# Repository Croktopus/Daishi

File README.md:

# Daishi

http://kb.metamechs.com/daishi/

I'm redesigning the Daishi-Prime (Daishi case that uses a plate), so stay tuned for that I guess.

If you're interested in designing your own keyboard, I recommend https://github.com/ruiqimao/keyboard-pcb-guide to learn PCB design, https://beta.docs.qmk.fm/ for how to use QMK, and https://www.youtube.com/watch?v=A5bc9c3S12g&list=PL40d7srwyc_Ow4aaOGXlP2idPGwD7ruKg to get started with Fusion 360.

Other invaluable resources:
* http://www.keyboard-layout-editor.com/ to design your layout
* http://builder.swillkb.com/ to generate a plate (though I do recommend doing it manually if it's going to be more complex than a rectangle with a few holes)
* https://discordapp.com/invite/Uq7gcHh for the QMK discord (super helpful folks who are way better at this than me)
* https://www.laserboost.com/ to get a metal plate cut
* https://www.ponoko.com/ to get an acrylic plate cut
* https://jlcpcb.com/ cheapest PCB manufacturer I've found

Check the BoM to find links to places where you can buy all the components for cheaper than I was able to.

All I ask is that if you do build one of these please send me pics!

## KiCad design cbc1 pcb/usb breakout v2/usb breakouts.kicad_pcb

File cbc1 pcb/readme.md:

# Making a PCB

If you just want to have a CBC1 PCB printed, you'll want to take the gerbers.zip file to your PCB fab of choice (I recommend JLCPCB for the price), as well as the gerbers.zip in the daughterboard directory.

I've also got all the KiCad files in here if you want to play around with making your own modifications.

Once you have your PCB (unless you got it assembled for you), you get to do all the super fun SMT soldering! This is easily the worst part of the process IMO, but you can get through it in a few hours. If you haven't done this before, look up some youtube tutorials before you decide whether you want to.

Then you can tune your stabs, crimp a cable, and solder some switches (I recommend following Nathan Kim's guide for stabilizers, just without the band-aid mod).

Obviously this is super light on details, but...anything in here that you don't know how to do, just look it up. If you're still having trouble understanding something, I can answer some questions, but there are some fairly deep topics in here that already have great educational resources (EEVBlog for soldering, https://github.com/ruiqimao/keyboard-pcb-guide for KiCad, Nathan Kim's vids and streams for keeb building).

But that's pretty much the gist of it for getting a functional PCB for your Daishi build.

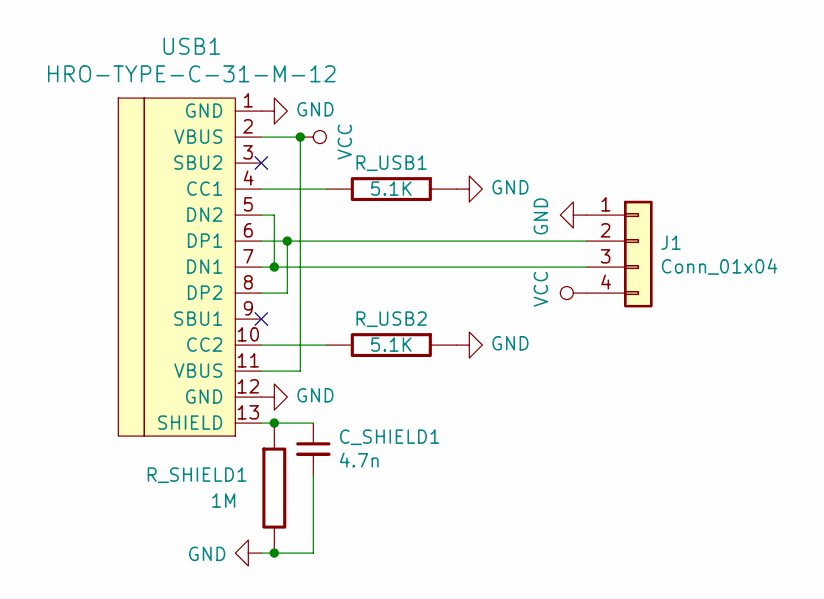
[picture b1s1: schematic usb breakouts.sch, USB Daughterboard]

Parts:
C_SHIELD1: 4.7n; C_0805_HandSoldering
J1: Conn_01x04; Pin_Header_Angled_1x04_Pitch2.54mm_centered
R_SHIELD1: 1M; R_0805_HandSoldering
R_USB1, R_USB2: 5.1K; R_0805_HandSoldering
USB1: HRO-TYPE-C-31-M-12; HRO-TYPE-C-31-M-12-HandSoldering

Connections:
GND: C_SHIELD1.2, J1.1, R_SHIELD1.2, R_USB1.1, R_USB2.1, USB1.1 (GND), USB1.12 (GND)
unnamed: C_SHIELD1.1, R_SHIELD1.1, USB1.13 (SHIELD)
unnamed: J1.2, USB1.6 (DP1), USB1.8 (DP2)
unnamed: J1.3, USB1.5 (DN2), USB1.7 (DN1)
unnamed: R_USB1.2, USB1.4 (CC1)
unnamed: R_USB2.2, USB1.10 (CC2)
VCC: J1.4, USB1.2 (VBUS), USB1.11 (VBUS)

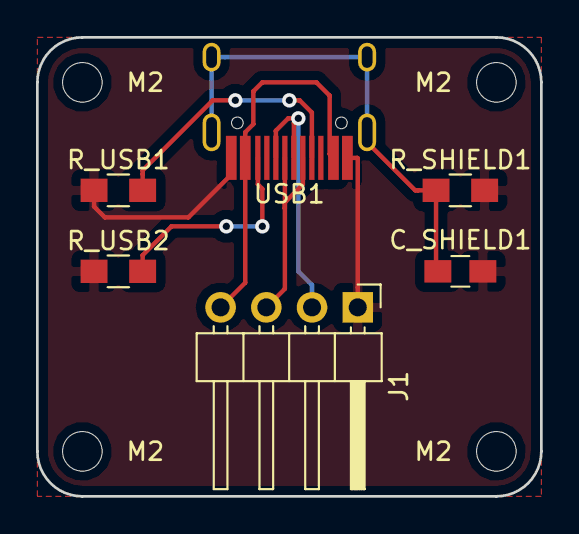
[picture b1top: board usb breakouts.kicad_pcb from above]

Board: 2 copper layers, 28.0 x 25.5 mm, 10 parts (0 on the bottom side), 7 nets.

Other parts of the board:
M2, M2#2, M2#3, M2#4: MountingHole_2.2mm_M2

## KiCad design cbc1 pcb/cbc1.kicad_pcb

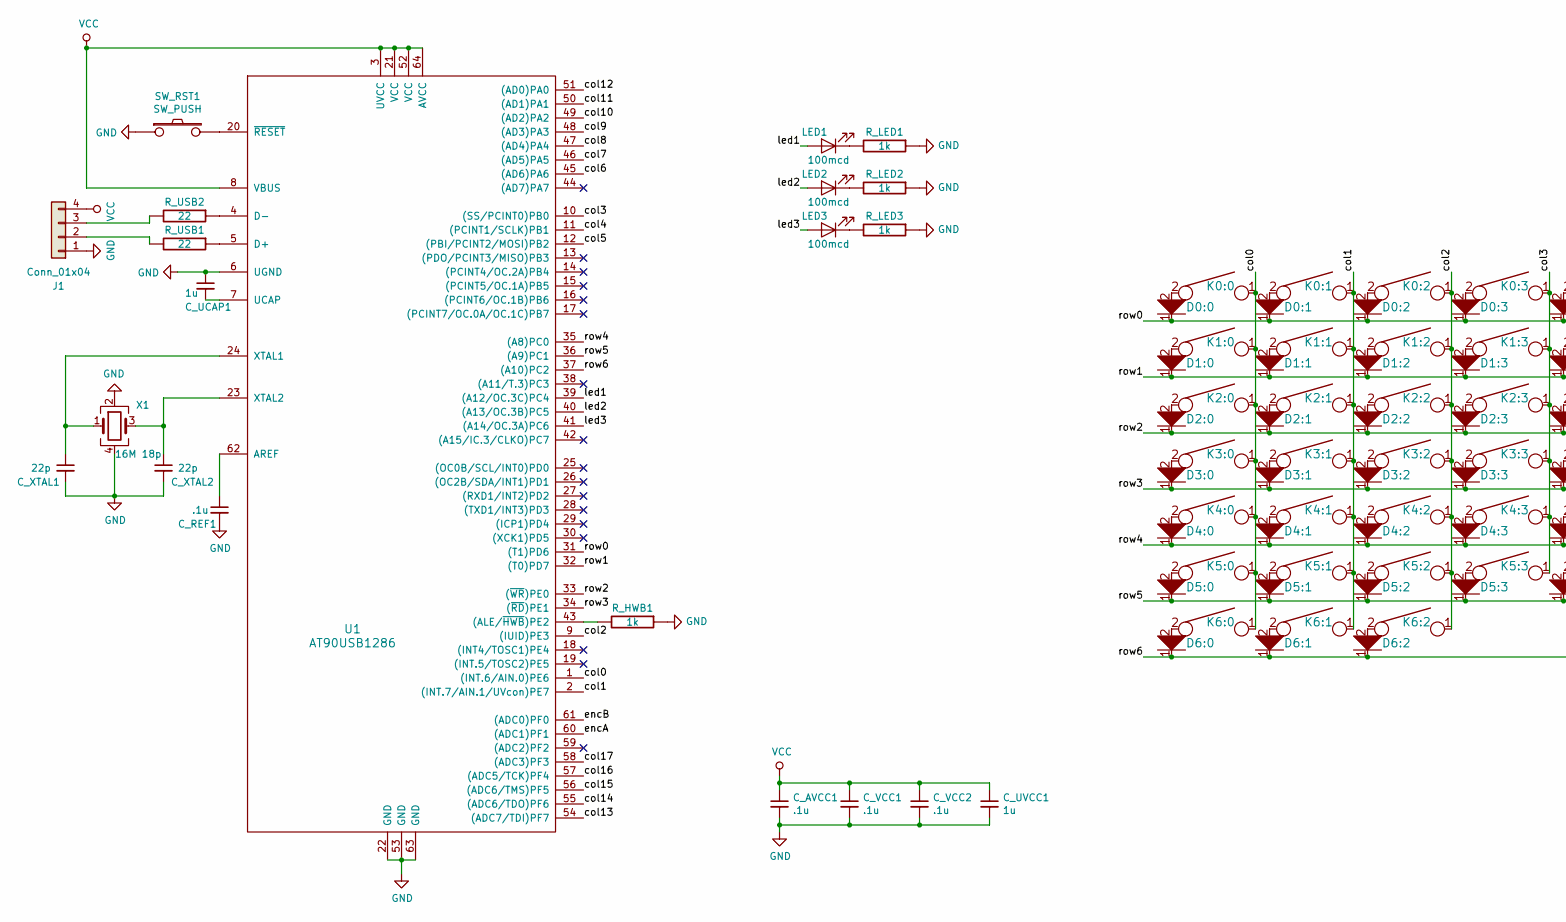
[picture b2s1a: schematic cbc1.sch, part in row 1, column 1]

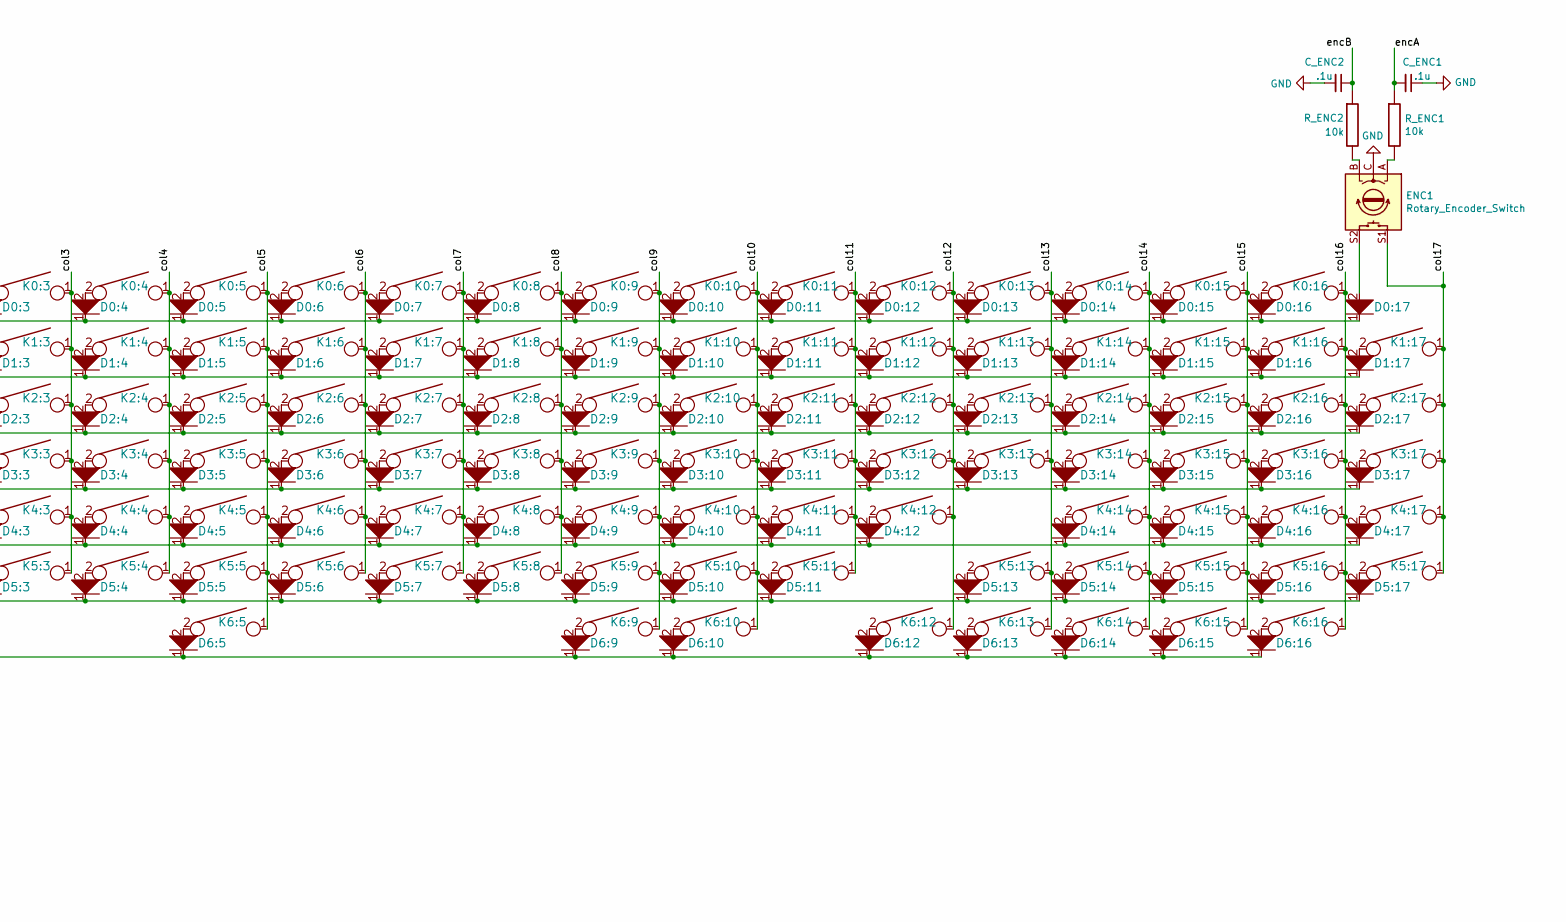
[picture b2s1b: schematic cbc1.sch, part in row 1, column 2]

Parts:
C_AVCC1: .1u; C_0805_HandSoldering
C_ENC1, C_ENC2: .1u; C_0805_HandSoldering
C_REF1: .1u; C_0805_HandSoldering
C_UCAP1: 1u; C_0805_HandSoldering
C_UVCC1: 1u; C_0805_HandSoldering
C_VCC1, C_VCC2: .1u; C_0805_HandSoldering
C_XTAL1, C_XTAL2: 22p; C_0805_HandSoldering
D0:0, D0:1, D0:2, D0:3, D0:4, D0:5, D0:6, D0:7, D0:8, D0:9, D0:10, D0:11, D0:12, D0:13, D0:14, D0:15, D0:16, D0:17, D1:0, D1:1, D1:2, D1:3, D1:4, D1:5, D1:6, D1:7, D1:8, D1:9, D1:10, D1:11, D1:12, D1:13, D1:14, D1:15, D1:16, D1:17, D2:0, D2:1, D2:2, D2:3, D2:4, D2:5, D2:6, D2:7, D2:8, D2:9, D2:10, D2:11, D2:12, D2:13, D2:14, D2:15, D2:16, D2:17, D3:0, D3:1, D3:2, D3:3, D3:4, D3:5, D3:6, D3:7, D3:8, D3:9, D3:10, D3:11, D3:12, D3:13, D3:14, D3:15, D3:16, D3:17, D4:0, D4:1, D4:2, D4:3, D4:4, D4:5, D4:6, D4:7, D4:8, D4:9, D4:10, D4:11, D4:12, D4:14, D4:15, D4:16, D4:17, D5:0, D5:1, D5:2, D5:3, D5:4, D5:5, D5:6, D5:7, D5:8, D5:9, D5:10, D5:11, D5:13, D5:14, D5:15, D5:16, D5:17, D6:0, D6:1, D6:2, D6:5, D6:9, D6:10, D6:12, D6:13, D6:14, D6:15, D6:16: D; D_SOD123_hand
ENC1: Rotary_Encoder_Switch; RotaryEncoder_Alps_EC11E-Switch_Vertical_H20mm
J1: Conn_01x04; Pin_Header_Angled_1x04_Pitch2.54mm
K0:0, K0:1, K0:2, K0:3, K0:4, K0:5, K0:6, K0:7, K0:8, K0:9, K0:10, K0:11, K0:12, K0:13, K0:14, K0:15, K0:16, K1:0, K1:1, K1:2, K1:3, K1:4, K1:5, K1:6, K1:7, K1:8, K1:9, K1:10, K1:11, K1:12, K1:13, K1:14, K1:15, K1:16, K1:17, K2:0, K2:1, K2:2, K2:3, K2:4, K2:5, K2:6, K2:7, K2:8, K2:9, K2:10, K2:11, K2:12, K2:14, K2:15, K2:16, K2:17, K3:1, K3:2, K3:3, K3:4, K3:5, K3:6, K3:7, K3:8, K3:9, K3:10, K3:11, K3:12, K3:14, K3:15, K3:16, K3:17, K4:1, K4:2, K4:3, K4:4, K4:5, K4:6, K4:7, K4:8, K4:9, K4:10, K4:11, K4:14, K4:15, K4:16, K4:17, K5:1, K5:2, K5:3, K5:4, K5:5, K5:6, K5:7, K5:8, K5:9, K5:10, K5:13, K5:14, K5:15, K5:16, K6:12, K6:13, K6:14, K6:15, K6:16: KEYSW; SMK-PCB-100-90deg
K2:13, K5:17: KEYSW; SMK-PCB-200-90deg
K3:0, K3:13, K6:9, K6:10: KEYSW; SMK-PCB-150-90deg
K4:0, K5:11: KEYSW; SMK-PCB-175-90deg
K4:12, K5:0: KEYSW; SMK-PCB-225-90deg
K6:0, K6:1, K6:2: KEYSW; SMK-PCB-125-90deg
K6:5: KEYSW; SMK-PCB-625-90deg
LED1, LED2, LED3: 100mcd; LED_0805_HandSoldering
R_ENC1, R_ENC2: 10k; R_0805_HandSoldering
R_HWB1: 1k; R_0805_HandSoldering
R_LED1, R_LED2, R_LED3: 1k; R_0805_HandSoldering
R_USB1, R_USB2: 22; R_0805_HandSoldering
SW_RST1: SW_PUSH; SW_SPST_TL3342
U1: AT90USB1286; TQFP-64_14x14mm_Pitch0.8mm
X1: 16M 18p; Crystal_SMD_SeikoEpson_FA238-4pin_3.2x2.5mm_HandSoldering

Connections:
/col0: K0:0.1, K1:0.1, K2:0.1, K3:0.1, K4:0.1, K5:0.1, K6:0.1, U1.1 ((INT.6/AIN.0)PE6)
/col1: K0:1.1, K1:1.1, K2:1.1, K3:1.1, K4:1.1, K5:1.1, K6:1.1, U1.2 ((INT.7/AIN.1/UVcon)PE7)
/col2: K0:2.1, K1:2.1, K2:2.1, K3:2.1, K4:2.1, K5:2.1, K6:2.1, U1.9 ((IUID)PE3)
/col3: K0:3.1, K1:3.1, K2:3.1, K3:3.1, K4:3.1, K5:3.1, U1.10 ((SS/PCINT0)PB0)
/col4: K0:4.1, K1:4.1, K2:4.1, K3:4.1, K4:4.1, K5:4.1, U1.11 ((PCINT1/SCLK)PB1)
/col5: K0:5.1, K1:5.1, K2:5.1, K3:5.1, K4:5.1, K5:5.1, K6:5.1, U1.12 ((PBI/PCINT2/MOSI)PB2)
/col6: K0:6.1, K1:6.1, K2:6.1, K3:6.1, K4:6.1, K5:6.1, U1.45 ((AD6)PA6)
/col7: K0:7.1, K1:7.1, K2:7.1, K3:7.1, K4:7.1, K5:7.1, U1.46 ((AD5)PA5)
/col8: K0:8.1, K1:8.1, K2:8.1, K3:8.1, K4:8.1, K5:8.1, U1.47 ((AD4)PA4)
/col9: K0:9.1, K1:9.1, K2:9.1, K3:9.1, K4:9.1, K5:9.1, K6:9.1, U1.48 ((AD3)PA3)
/col10: K0:10.1, K1:10.1, K2:10.1, K3:10.1, K4:10.1, K5:10.1, K6:10.1, U1.49 ((AD2)PA2)
/col11: K0:11.1, K1:11.1, K2:11.1, K3:11.1, K4:11.1, K5:11.1, U1.50 ((AD1)PA1)
/col12: K0:12.1, K1:12.1, K2:12.1, K3:12.1, K4:12.1, K6:12.1, U1.51 ((AD0)PA0)
/col13: K0:13.1, K1:13.1, K2:13.1, K3:13.1, K5:13.1, K6:13.1, U1.54 ((ADC7/TDI)PF7)
/col14: K0:14.1, K1:14.1, K2:14.1, K3:14.1, K4:14.1, K5:14.1, K6:14.1, U1.55 ((ADC6/TDO)PF6)
/col15: K0:15.1, K1:15.1, K2:15.1, K3:15.1, K4:15.1, K5:15.1, K6:15.1, U1.56 ((ADC6/TMS)PF5)
/col16: K0:16.1, K1:16.1, K2:16.1, K3:16.1, K4:16.1, K5:16.1, K6:16.1, U1.57 ((ADC5/TCK)PF4)
/col17: ENC1.S1, K1:17.1, K2:17.1, K3:17.1, K4:17.1, K5:17.1, U1.58 ((ADC3)PF3)
/encA: C_ENC1.2, R_ENC1.1, U1.60 ((ADC1)PF1)
/encB: C_ENC2.1, R_ENC2.1, U1.61 ((ADC0)PF0)
/led1: LED1.2 (A), U1.39 ((A12/OC.3C)PC4)
/led2: LED2.2 (A), U1.40 ((A13/OC.3B)PC5)
/led3: LED3.2 (A), U1.41 ((A14/OC.3A)PC6)
/row0: D0:0.1, D0:1.1, D0:2.1, D0:3.1, D0:4.1, D0:5.1, D0:6.1, D0:7.1, D0:8.1, D0:9.1, D0:10.1, D0:11.1, D0:12.1, D0:13.1, D0:14.1, D0:15.1, D0:16.1, D0:17.1, U1.31 ((T1)PD6)
/row1: D1:0.1, D1:1.1, D1:2.1, D1:3.1, D1:4.1, D1:5.1, D1:6.1, D1:7.1, D1:8.1, D1:9.1, D1:10.1, D1:11.1, D1:12.1, D1:13.1, D1:14.1, D1:15.1, D1:16.1, D1:17.1, U1.32 ((T0)PD7)
/row2: D2:0.1, D2:1.1, D2:2.1, D2:3.1, D2:4.1, D2:5.1, D2:6.1, D2:7.1, D2:8.1, D2:9.1, D2:10.1, D2:11.1, D2:12.1, D2:13.1, D2:14.1, D2:15.1, D2:16.1, D2:17.1, U1.33 ((~WR~)PE0)
/row3: D3:0.1, D3:1.1, D3:2.1, D3:3.1, D3:4.1, D3:5.1, D3:6.1, D3:7.1, D3:8.1, D3:9.1, D3:10.1, D3:11.1, D3:12.1, D3:13.1, D3:14.1, D3:15.1, D3:16.1, D3:17.1, U1.34 ((~RD~)PE1)
/row4: D4:0.1, D4:1.1, D4:2.1, D4:3.1, D4:4.1, D4:5.1, D4:6.1, D4:7.1, D4:8.1, D4:9.1, D4:10.1, D4:11.1, D4:12.1, D4:14.1, D4:15.1, D4:16.1, D4:17.1, U1.35 ((A8)PC0)
/row5: D5:0.1, D5:1.1, D5:2.1, D5:3.1, D5:4.1, D5:5.1, D5:6.1, D5:7.1, D5:8.1, D5:9.1, D5:10.1, D5:11.1, D5:13.1, D5:14.1, D5:15.1, D5:16.1, D5:17.1, U1.36 ((A9)PC1)
/row6: D6:0.1, D6:1.1, D6:2.1, D6:5.1, D6:9.1, D6:10.1, D6:12.1, D6:13.1, D6:14.1, D6:15.1, D6:16.1, U1.37 ((A10)PC2)
GND: C_AVCC1.2, C_ENC1.1, C_ENC2.2, C_REF1.2, C_UCAP1.1, C_UVCC1.2, C_VCC1.2, C_VCC2.2, C_XTAL1.2, C_XTAL2.2, ENC1.C, J1.1, R_HWB1.1, R_LED1.1, R_LED2.1, R_LED3.1, SW_RST1.1, U1.6 (UGND), U1.22 (GND), U1.53 (GND), U1.63 (GND), X1.2, X1.4
unnamed: C_REF1.1, U1.62 (AREF)
unnamed: C_UCAP1.2, U1.7 (UCAP)
unnamed: C_XTAL1.1, U1.24 (XTAL1), X1.1
unnamed: C_XTAL2.1, U1.23 (XTAL2), X1.3
unnamed: D0:0.2, K0:0.2
unnamed: D0:1.2, K0:1.2
unnamed: D0:2.2, K0:2.2
unnamed: D0:3.2, K0:3.2
unnamed: D0:4.2, K0:4.2
unnamed: D0:5.2, K0:5.2
unnamed: D0:6.2, K0:6.2
unnamed: D0:7.2, K0:7.2
unnamed: D0:8.2, K0:8.2
unnamed: D0:9.2, K0:9.2
unnamed: D0:10.2, K0:10.2
unnamed: D0:11.2, K0:11.2
unnamed: D0:12.2, K0:12.2
unnamed: D0:13.2, K0:13.2
unnamed: D0:14.2, K0:14.2
unnamed: D0:15.2, K0:15.2
unnamed: D0:16.2, K0:16.2
unnamed: D0:17.2, ENC1.S2
unnamed: D1:0.2, K1:0.2
unnamed: D1:1.2, K1:1.2
unnamed: D1:2.2, K1:2.2
unnamed: D1:3.2, K1:3.2
unnamed: D1:4.2, K1:4.2
unnamed: D1:5.2, K1:5.2
unnamed: D1:6.2, K1:6.2
unnamed: D1:7.2, K1:7.2
unnamed: D1:8.2, K1:8.2
unnamed: D1:9.2, K1:9.2
unnamed: D1:10.2, K1:10.2
unnamed: D1:11.2, K1:11.2
unnamed: D1:12.2, K1:12.2
unnamed: D1:13.2, K1:13.2
unnamed: D1:14.2, K1:14.2
unnamed: D1:15.2, K1:15.2
unnamed: D1:16.2, K1:16.2
unnamed: D1:17.2, K1:17.2
unnamed: D2:0.2, K2:0.2
unnamed: D2:1.2, K2:1.2
unnamed: D2:2.2, K2:2.2
unnamed: D2:3.2, K2:3.2
unnamed: D2:4.2, K2:4.2
unnamed: D2:5.2, K2:5.2
unnamed: D2:6.2, K2:6.2
unnamed: D2:7.2, K2:7.2
unnamed: D2:8.2, K2:8.2
unnamed: D2:9.2, K2:9.2
unnamed: D2:10.2, K2:10.2
unnamed: D2:11.2, K2:11.2
unnamed: D2:12.2, K2:12.2
unnamed: D2:13.2, K2:13.2
unnamed: D2:14.2, K2:14.2
unnamed: D2:15.2, K2:15.2
unnamed: D2:16.2, K2:16.2
unnamed: D2:17.2, K2:17.2
unnamed: D3:0.2, K3:0.2
unnamed: D3:1.2, K3:1.2
unnamed: D3:2.2, K3:2.2
unnamed: D3:3.2, K3:3.2
unnamed: D3:4.2, K3:4.2
unnamed: D3:5.2, K3:5.2
unnamed: D3:6.2, K3:6.2
unnamed: D3:7.2, K3:7.2
unnamed: D3:8.2, K3:8.2
unnamed: D3:9.2, K3:9.2
unnamed: D3:10.2, K3:10.2
unnamed: D3:11.2, K3:11.2
unnamed: D3:12.2, K3:12.2
unnamed: D3:13.2, K3:13.2
unnamed: D3:14.2, K3:14.2
unnamed: D3:15.2, K3:15.2
unnamed: D3:16.2, K3:16.2
unnamed: D3:17.2, K3:17.2
unnamed: D4:0.2, K4:0.2
unnamed: D4:1.2, K4:1.2
unnamed: D4:2.2, K4:2.2
unnamed: D4:3.2, K4:3.2
unnamed: D4:4.2, K4:4.2
unnamed: D4:5.2, K4:5.2
unnamed: D4:6.2, K4:6.2
unnamed: D4:7.2, K4:7.2
unnamed: D4:8.2, K4:8.2
unnamed: D4:9.2, K4:9.2
unnamed: D4:10.2, K4:10.2
unnamed: D4:11.2, K4:11.2
unnamed: D4:12.2, K4:12.2
unnamed: D4:14.2, K4:14.2
unnamed: D4:15.2, K4:15.2
unnamed: D4:16.2, K4:16.2
unnamed: D4:17.2, K4:17.2
unnamed: D5:0.2, K5:0.2
unnamed: D5:1.2, K5:1.2
unnamed: D5:2.2, K5:2.2
unnamed: D5:3.2, K5:3.2
unnamed: D5:4.2, K5:4.2
unnamed: D5:5.2, K5:5.2
unnamed: D5:6.2, K5:6.2
unnamed: D5:7.2, K5:7.2
unnamed: D5:8.2, K5:8.2
unnamed: D5:9.2, K5:9.2
unnamed: D5:10.2, K5:10.2
unnamed: D5:11.2, K5:11.2
unnamed: D5:13.2, K5:13.2
unnamed: D5:14.2, K5:14.2
unnamed: D5:15.2, K5:15.2
unnamed: D5:16.2, K5:16.2
unnamed: D5:17.2, K5:17.2
unnamed: D6:0.2, K6:0.2
unnamed: D6:1.2, K6:1.2
unnamed: D6:2.2, K6:2.2
unnamed: D6:5.2, K6:5.2
unnamed: D6:9.2, K6:9.2
unnamed: D6:10.2, K6:10.2
unnamed: D6:12.2, K6:12.2
unnamed: D6:13.2, K6:13.2
unnamed: D6:14.2, K6:14.2
unnamed: D6:15.2, K6:15.2
unnamed: D6:16.2, K6:16.2
unnamed: ENC1.A, R_ENC1.2
unnamed: ENC1.B, R_ENC2.2
unnamed: J1.2, R_USB1.2
unnamed: J1.3, R_USB2.2
unnamed: LED1.1 (K), R_LED1.2
unnamed: LED2.1 (K), R_LED2.2
unnamed: LED3.1 (K), R_LED3.2
unnamed: R_HWB1.2, U1.43 ((ALE/~HWB~)PE2)
unnamed: R_USB1.1, U1.5 (D+)
unnamed: R_USB2.1, U1.4 (D-)
unnamed: SW_RST1.2, U1.20 (~RESET)
VCC: C_AVCC1.1, C_UVCC1.1, C_VCC1.1, C_VCC2.1, J1.4, U1.3 (UVCC), U1.8 (VBUS), U1.21 (VCC), U1.52 (VCC), U1.64 (AVCC)

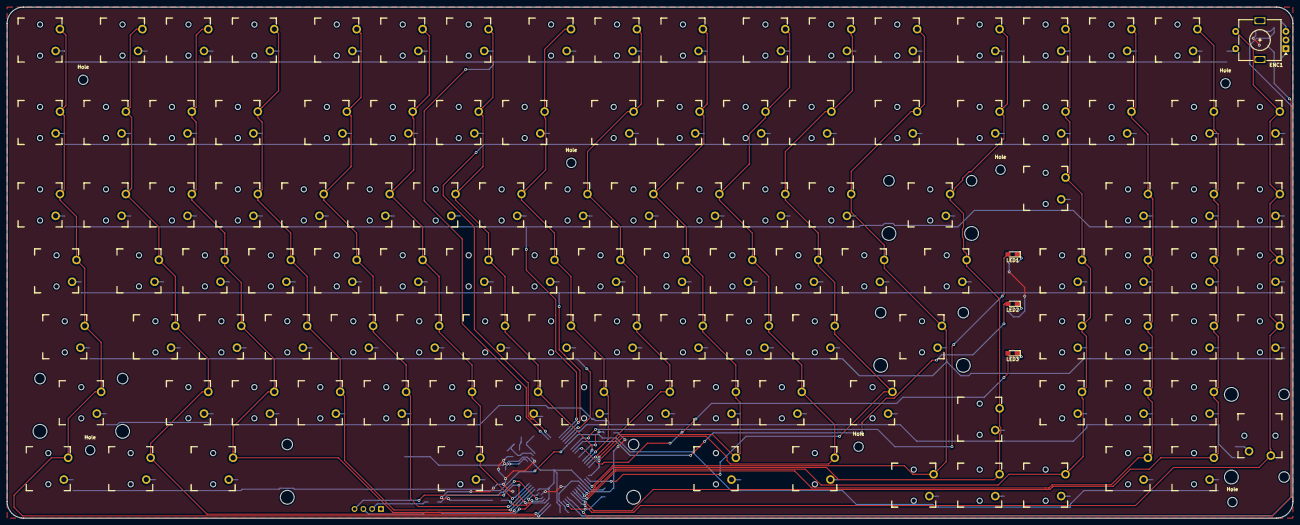
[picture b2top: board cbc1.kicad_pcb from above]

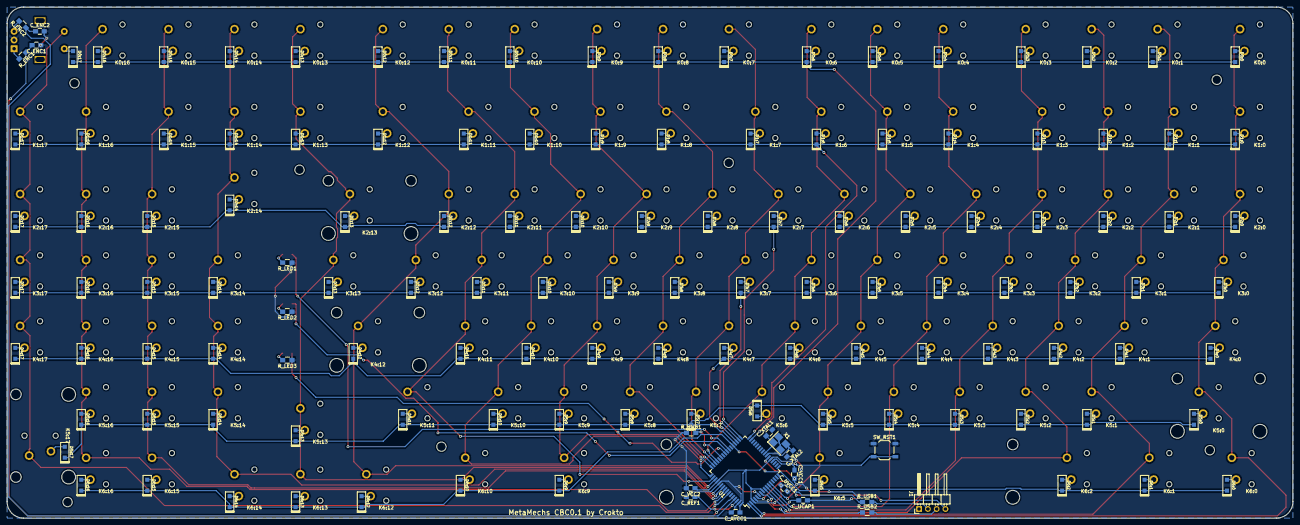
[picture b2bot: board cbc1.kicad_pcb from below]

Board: 2 copper layers, 371.5 x 147.6 mm, 266 parts (139 on the bottom side), 164 nets.

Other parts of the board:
Hole: M2.5; MountingHole_2.7mm_M2.5
Hole#2, Hole#3, Hole#4, Hole#5, Hole#6, Hole#7: M2.5; MountingHole_2.7mm_M2.5

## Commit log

2019-03-20 adding local versions
2019-03-20 changing name of f3d file
2019-03-25 updating top case gaps, adding plate file
2019-03-25 added bom
2019-03-27 updating files
    readme, stls, f3d
2019-03-28 added short walk-through-esque readmes
2019-03-29 updated case readme
2019-04-25 Reformatted firmware
2019-04-26 fixed typo
2019-05-03 fixed dumb mistake
